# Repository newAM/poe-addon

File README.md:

# PoE Addon

Simple board to add power over Ethernet to a project.

This uses the [Wiznet W5500] for TCP/IP offload, and a [Microchip 25AA02E48] for
a valid EUI-48 MAC address.

## Bill of Materials

A bill of materials generated by [InteractiveHtmlBom] can be viewed at <https://newam.github.io/poe-addon/>

## Media

## Software Used

- [KiCad](http://kicad.org/) 7.0.0 release

[InteractiveHtmlBom]: https://github.com/openscopeproject/InteractiveHtmlBom/issues
[Wiznet W5500]: https://www.wiznet.io/product-item/w5500/
[Microchip 25AA02E48]: http://ww1.microchip.com/downloads/en/devicedoc/22123a.pdf

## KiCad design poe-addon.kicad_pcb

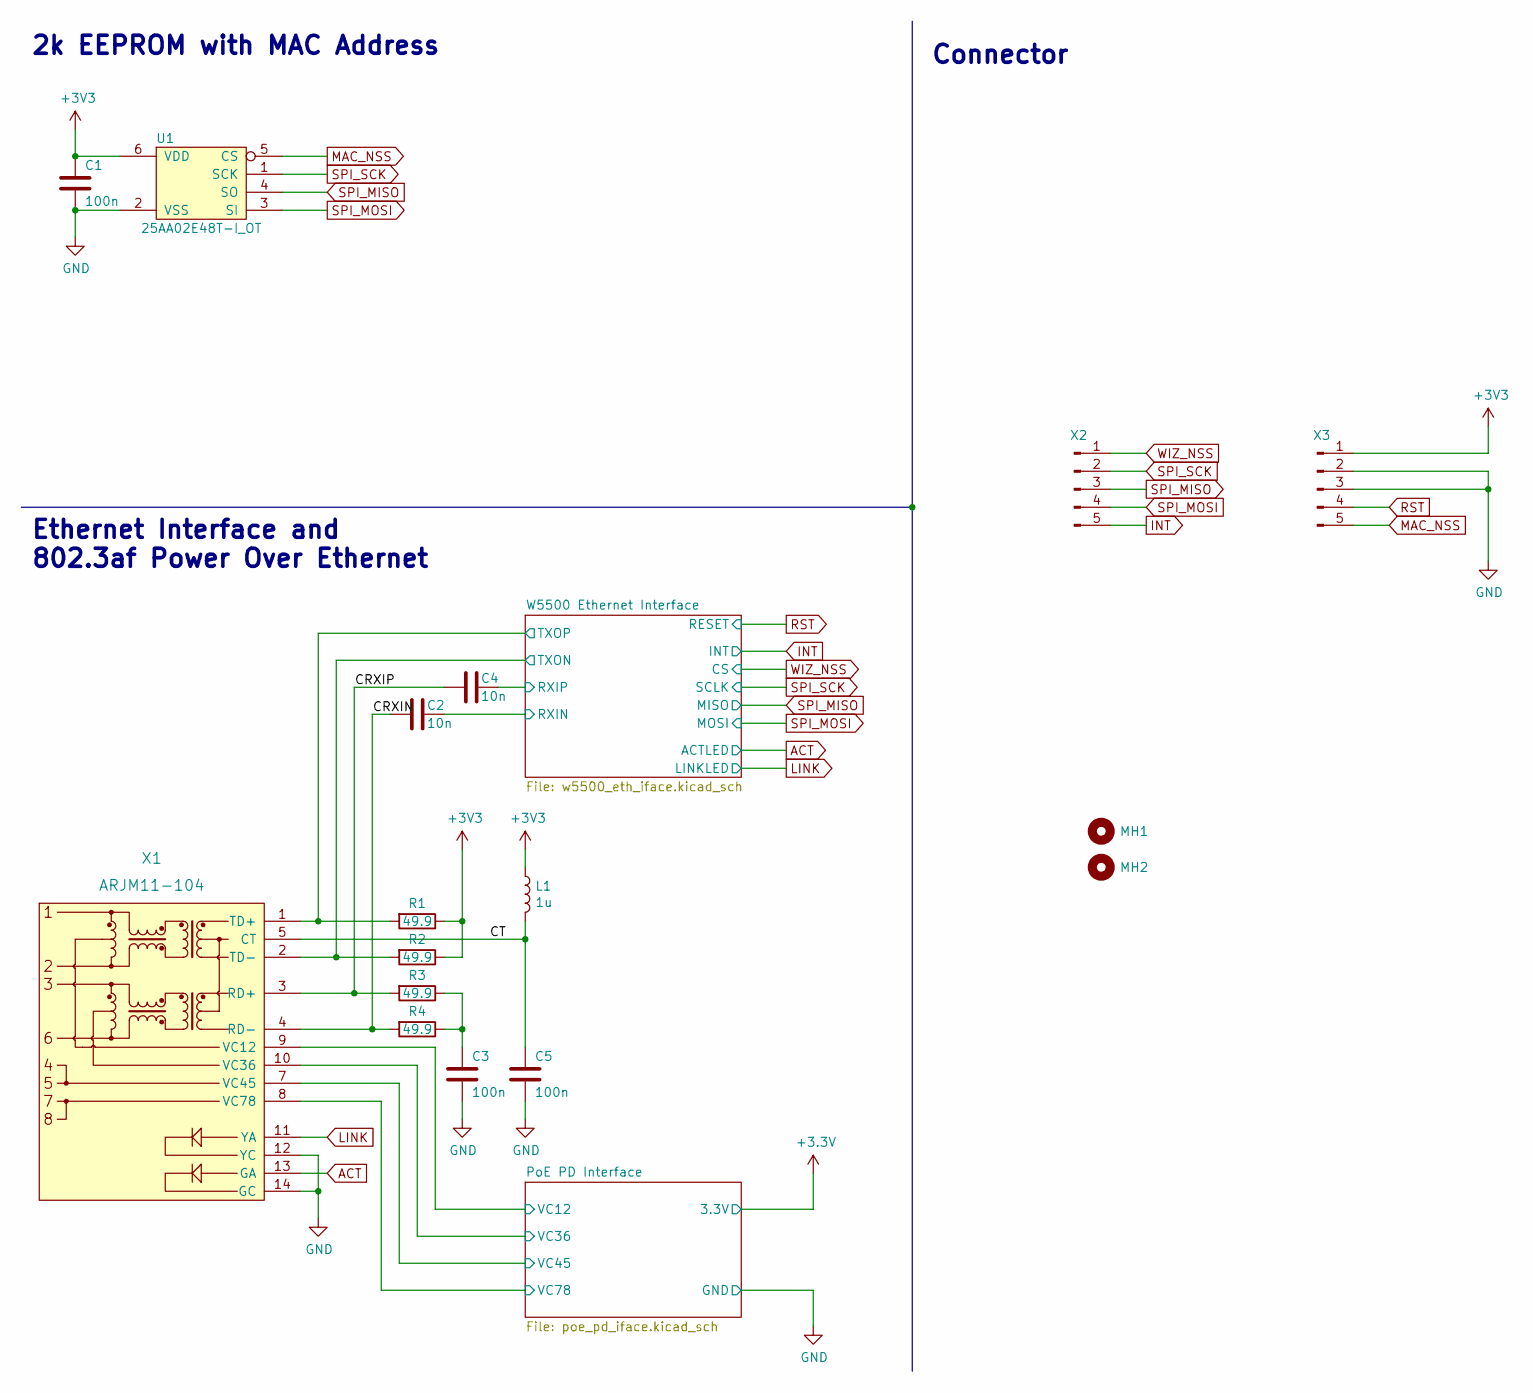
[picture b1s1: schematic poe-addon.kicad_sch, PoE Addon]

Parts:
C1, C3, C5: 100n; C_0603_1608Metric; Tolerance 10%; Voltage 16; DigiKey Part Number 1276-1005-1-ND
C2, C4: 10n; C_0603_1608Metric; Tolerance 10%; Voltage 50V; DigiKey Part Number 1276-1009-1-ND
L1: 1u; L_0603_1608Metric; Tolerance 20%; DigiKey Part Number 445-3163-1-ND
MH1, MH2: MountingHole; MountingHole_3.2mm_M3
R1, R2, R3, R4: 49.9; R_0805_2012Metric; Tolerance 1%; DigiKey Part Number RNCP0805FTD49R9CT-ND
U1: 25AA02E48T-I_OT; SOT-23-6; DigiKey Part Number 25AA02E48T-I/OT
X1: ARJM11-104; ARJM11D7-104-AB-EW2; DigiKey Part Number 535-14150-ND
X2, X3: Conn_01x05_Male; PinHeader_1x05_P2.54mm_Vertical

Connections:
/CRXIN: C2.2, R4.2, X1.4 (RD-)
/CRXIP: C4.2, R3.2, X1.3 (RD+)
/CT: C5.1, L1.2, X1.5 (CT)
/PoE PD Interface/VC12: X1.9 (VC12); also elsewhere on the board
/PoE PD Interface/VC36: X1.10 (VC36); also elsewhere on the board
/PoE PD Interface/VC45: X1.7 (VC45); also elsewhere on the board
/PoE PD Interface/VC78: X1.8 (VC78); also elsewhere on the board
/W5500 Ethernet Interface/RXIN: C2.1; also elsewhere on the board
/W5500 Ethernet Interface/RXIP: C4.1; also elsewhere on the board
/W5500 Ethernet Interface/TXON: R2.2, X1.2 (TD-); also elsewhere on the board
/W5500 Ethernet Interface/TXOP: R1.2, X1.1 (TD+); also elsewhere on the board
ACT: X1.13 (GA); also elsewhere on the board
GND: C1.2, C3.2, C5.2, U1.2 (VSS), X1.12 (YC), X1.14 (GC), X3.2, X3.3; also elsewhere on the board
INT: X2.5; also elsewhere on the board
LINK: X1.11 (YA); also elsewhere on the board
MAC_NSS: U1.5 (CS), X3.5
unnamed: C3.1, R3.1, R4.1
RST: X3.4; also elsewhere on the board
SPI_MISO: U1.4 (SO), X2.3; also elsewhere on the board
SPI_MOSI: U1.3 (SI), X2.4; also elsewhere on the board
SPI_SCK: U1.1 (SCK), X2.2; also elsewhere on the board
WIZ_NSS: X2.1; also elsewhere on the board

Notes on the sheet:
2k EEPROM with MAC Address
Connector
Ethernet Interface and 802.3af Power Over Ethernet

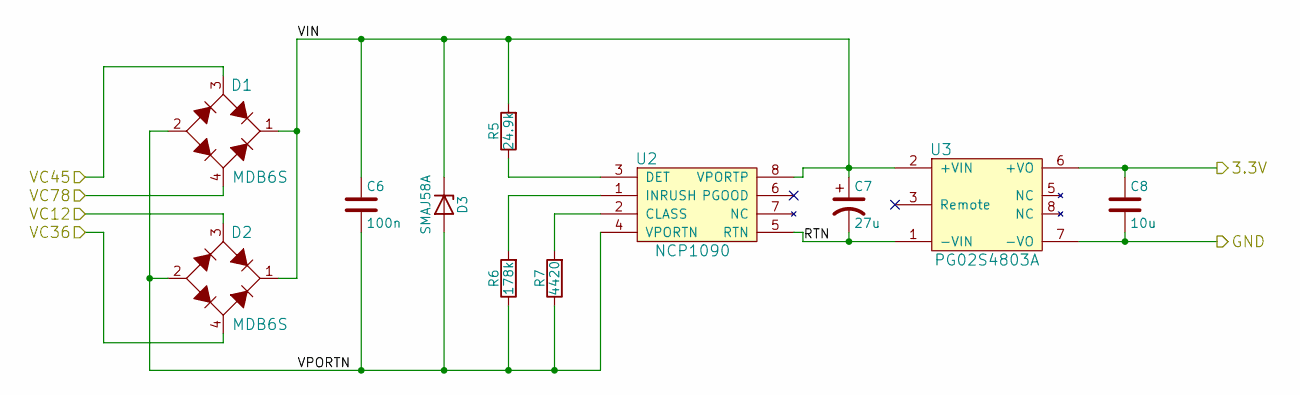
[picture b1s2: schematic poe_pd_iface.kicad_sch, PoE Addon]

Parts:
C6: 100n; C_0805_2012Metric; DigiKey Part Number 1276-6840-1-ND
C7: 27u; CP_Elec_8x10.5; DigiKey Part Number 399-A768KE276M1JLAE054CT-ND
C8: 10u; C_0805_2012Metric; DigiKey Part Number 1276-6456-1-ND
D1, D2: MDB6S; Micro-DIP-4; DigiKey Part Number MDB6SFSCT-ND
D3: SMAJ58A; D_SMA; DigiKey Part Number SMAJ58A-E3/61GICT-ND
R5: 24.9k; R_0603_1608Metric; DigiKey Part Number 311-24.9KHRCT-ND
R6: 178k; R_0603_1608Metric; DigiKey Part Number 311-178KHRCT-ND
R7: 4420; R_0603_1608Metric; DigiKey Part Number 311-4.42KHRCT-ND
U2: NCP1090; SOIC-8_3.9x4.9mm_P1.27mm; DigiKey Part Number NCP1090DRGOSCT-ND
U3: PG02S4803A; PG02S; DigiKey Part Number 941-1185-ND

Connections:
/PoE PD Interface/RTN: C7.2, U2.5 (RTN), U3.1 (-VIN)
/PoE PD Interface/VC12: D2.3 (AC1); also elsewhere on the board
/PoE PD Interface/VC36: D2.4 (AC2); also elsewhere on the board
/PoE PD Interface/VC45: D1.3 (AC1); also elsewhere on the board
/PoE PD Interface/VC78: D1.4 (AC2); also elsewhere on the board
/PoE PD Interface/VIN: C6.1, C7.1, D1.1 (+), D2.1 (+), D3.1 (K), R5.2, U2.8 (VPORTP), U3.2 (+VIN)
/PoE PD Interface/VPORTN: C6.2, D1.2 (-), D2.2 (-), D3.2 (A), R6.1, R7.1, U2.4 (VPORTN)
GND: C8.2, U3.7 (-VO); also elsewhere on the board
unnamed: R5.1, U2.3 (DET)
unnamed: R6.2, U2.1 (INRUSH)
unnamed: R7.2, U2.2 (CLASS)

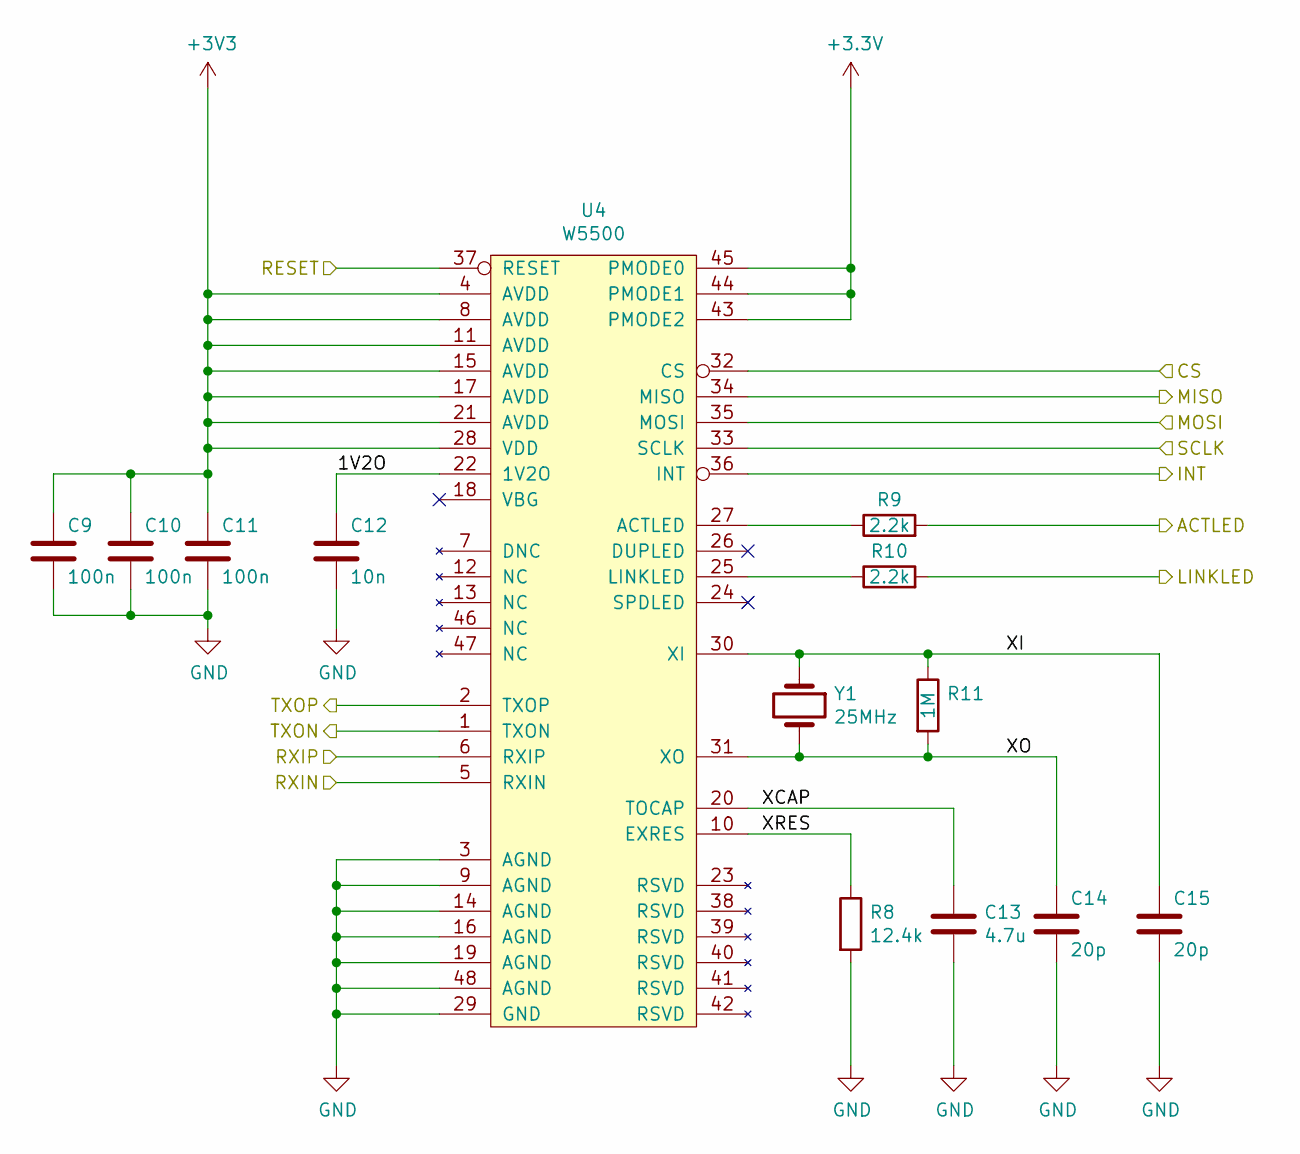
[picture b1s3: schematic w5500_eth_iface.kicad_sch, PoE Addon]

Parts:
C9, C10, C11: 100n; C_0603_1608Metric; DigiKey Part Number 1276-1012-1-ND
C12: 10n; C_0603_1608Metric; DigiKey Part Number 1276-1009-1-ND
C13: 4.7u; C_0603_1608Metric; DigiKey Part Number 1276-1907-1-ND
C14, C15: 20p; C_0603_1608Metric; DigiKey Part Number 1276-1187-1-ND
R8: 12.4k; R_0603_1608Metric; Tolerance ±1%; DigiKey Part Number 311-12.4KHRCT-ND
R9, R10: 2.2k; R_0603_1608Metric; DigiKey Part Number 311-2.20KHRCT-ND
R11: 1M; R_0603_1608Metric; DigiKey Part Number 311-1.0MGRCT-ND
U4: W5500; LQFP-48_7x7mm_P0.5mm; DigiKey Part Number 1278-1021-ND
Y1: 25MHz; Crystal_SMD_5032-2Pin_5.0x3.2mm; DigiKey Part Number CTX1175CT-ND

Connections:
/W5500 Ethernet Interface/1V2O: C12.1, U4.22 (1V2O)
/W5500 Ethernet Interface/RXIN: U4.5 (RXIN); also elsewhere on the board
/W5500 Ethernet Interface/RXIP: U4.6 (RXIP); also elsewhere on the board
/W5500 Ethernet Interface/TXON: U4.1 (TXON); also elsewhere on the board
/W5500 Ethernet Interface/TXOP: U4.2 (TXOP); also elsewhere on the board
/W5500 Ethernet Interface/XCAP: C13.1, U4.20 (TOCAP)
/W5500 Ethernet Interface/XI: C15.1, R11.1, U4.30 (XI), Y1.1
/W5500 Ethernet Interface/XO: C14.1, R11.2, U4.31 (XO), Y1.2
/W5500 Ethernet Interface/XRES: R8.1, U4.10 (EXRES)
ACT: R9.2; also elsewhere on the board
GND: C9.2, C10.2, C11.2, C12.2, C13.2, C14.2, C15.2, R8.2, U4.3 (AGND), U4.9 (AGND), U4.14 (AGND), U4.16 (AGND), U4.19 (AGND), U4.29 (GND), U4.48 (AGND); also elsewhere on the board
INT: U4.36 (INT); also elsewhere on the board
LINK: R10.2; also elsewhere on the board
unnamed: R9.1, U4.27 (ACTLED)
unnamed: R10.1, U4.25 (LINKLED)
RST: U4.37 (RESET); also elsewhere on the board
SPI_MISO: U4.34 (MISO); also elsewhere on the board
SPI_MOSI: U4.35 (MOSI); also elsewhere on the board
SPI_SCK: U4.33 (SCLK); also elsewhere on the board
WIZ_NSS: U4.32 (CS); also elsewhere on the board

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
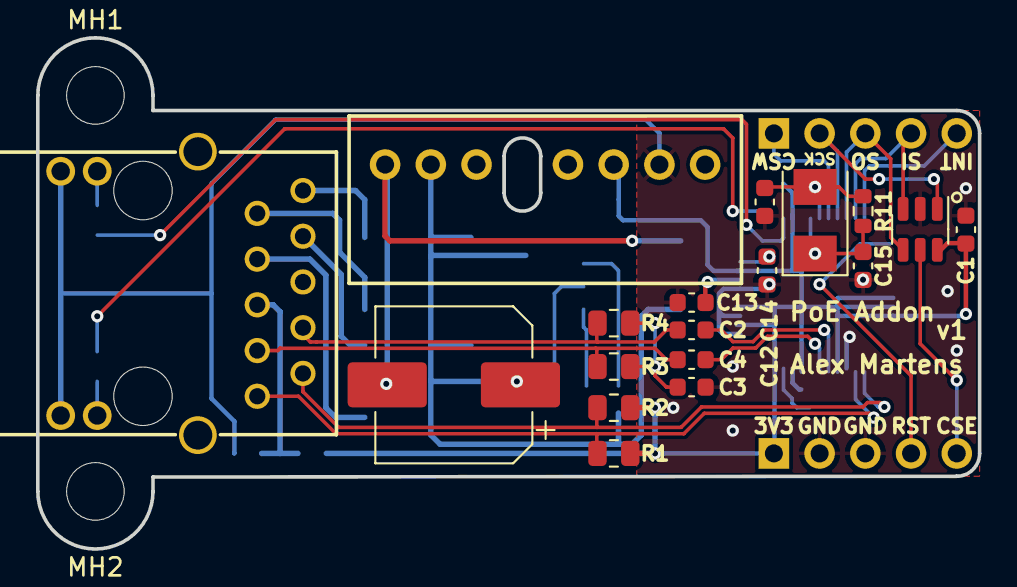
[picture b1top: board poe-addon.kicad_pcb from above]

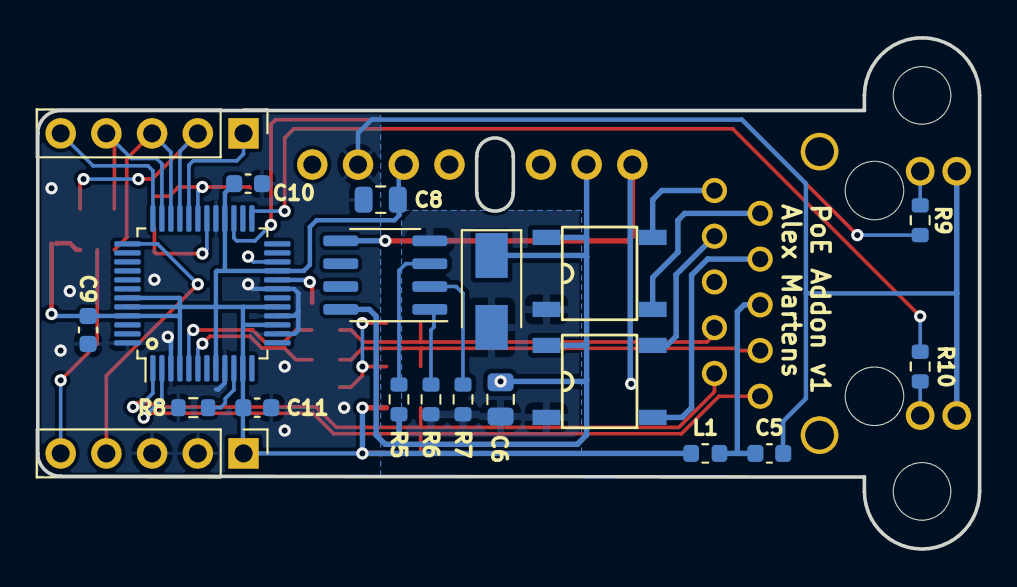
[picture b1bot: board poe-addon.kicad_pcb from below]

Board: 2 copper layers, 52.3 x 28.4 mm, 40 parts (20 on the bottom side), 36 nets.

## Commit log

2022-04-15 fix typo
2022-06-26 add pg02s 3D model
2022-06-26 Add interactive bill of materials
2022-06-26 README: add link to BOM
2022-06-26 bom: add digikey part numbers
2022-06-26 10nF 0603: 1276-1921-1-ND -> 1276-1009-1-ND
2022-06-26 NCP1090: NCP1090DGOS-ND -> NCP1090DRGOSCT-ND
2022-06-26 22uF electrolytic: replace with 27uF for stock reasons
    399-A768KE226M1JLAE054TR-ND -> 399-A768KE276M1JLAE054CT-ND
2022-06-26 w5500 crystal: CTX1437CT-ND -> CTX1175CT-ND
2022-06-27 add mounting holes, replace magjack with in-stock part
2022-06-27 flake.nix: remove patch from InteractiveHtmlBom
2022-06-27 update date
2022-06-27 deploy: e2dd724646c237e0e1d556927b6f1ff099d4cfc5
2022-10-13 CI: bump cachix actions
2022-10-28 Bump cachix/cachix-action from 11 to 12
    Bumps [cachix/cachix-action](https://github.com/cachix/cachix-action) from 11 to 12.
    - [Release notes](https://github.com/cachix/cachix-action/releases)
    - [Commits](https://github.com/cachix/cachix-action/compare/v11...v12)
    ---
    updated-dependencies:
    - dependency-name: cachix/cachix-action
2023-02-07 Bump cachix/install-nix-action from 18 to 19
    Bumps [cachix/install-nix-action](https://github.com/cachix/install-nix-action) from 18 to 19.
    - [Release notes](https://github.com/cachix/install-nix-action/releases)
    - [Commits](https://github.com/cachix/install-nix-action/compare/v18...v19)
    ---
    updated-dependencies:
    - dependency-name: cachix/install-nix-action
2023-03-02 Bump cachix/install-nix-action from 19 to 20
    Bumps [cachix/install-nix-action](https://github.com/cachix/install-nix-action) from 19 to 20.
    - [Release notes](https://github.com/cachix/install-nix-action/releases)
    - [Commits](https://github.com/cachix/install-nix-action/compare/v19...v20)
    ---
    updated-dependencies:
    - dependency-name: cachix/install-nix-action
2023-05-25 Bump cachix/install-nix-action from 20 to 21
    Bumps [cachix/install-nix-action](https://github.com/cachix/install-nix-action) from 20 to 21.
    - [Release notes](https://github.com/cachix/install-nix-action/releases)
    - [Commits](https://github.com/cachix/install-nix-action/compare/v20...v21)
    ---
    updated-dependencies:
    - dependency-name: cachix/install-nix-action
2023-06-19 Bump cachix/install-nix-action from 21 to 22
    Bumps [cachix/install-nix-action](https://github.com/cachix/install-nix-action) from 21 to 22.
    - [Release notes](https://github.com/cachix/install-nix-action/releases)
    - [Commits](https://github.com/cachix/install-nix-action/compare/v21...v22)
    ---
    updated-dependencies:
    - dependency-name: cachix/install-nix-action
2023-07-15 flake.lock: update
    • Updated input 'nixpkgs':
    'github:nixos/nixpkgs/f2537a505d45c31fe5d9c27ea9829b6f4c4e6ac5' (2022-06-26)
    → 'github:nixos/nixpkgs/e74e68449c385db82de3170288a28cd0f608544f' (2023-07-13)
2023-07-18 Add LCSC part numbers
2023-09-05 Bump actions/checkout from 3 to 4
    Bumps [actions/checkout](https://github.com/actions/checkout) from 3 to 4.
    - [Release notes](https://github.com/actions/checkout/releases)
    - [Changelog](https://github.com/actions/checkout/blob/main/CHANGELOG.md)
    - [Commits](https://github.com/actions/checkout/compare/v3...v4)
    ---
    updated-dependencies:
2023-09-05 Bump cachix/install-nix-action from 22 to 23
    Bumps [cachix/install-nix-action](https://github.com/cachix/install-nix-action) from 22 to 23.
    - [Release notes](https://github.com/cachix/install-nix-action/releases)
    - [Commits](https://github.com/cachix/install-nix-action/compare/v22...v23)
    ---
    updated-dependencies:
    - dependency-name: cachix/install-nix-action
2023-11-29 Bump cachix/cachix-action from 12 to 13
    Bumps [cachix/cachix-action](https://github.com/cachix/cachix-action) from 12 to 13.
    - [Release notes](https://github.com/cachix/cachix-action/releases)
    - [Commits](https://github.com/cachix/cachix-action/compare/v12...v13)
    ---
    updated-dependencies:
    - dependency-name: cachix/cachix-action
2023-11-29 Bump cachix/install-nix-action from 23 to 24
    Bumps [cachix/install-nix-action](https://github.com/cachix/install-nix-action) from 23 to 24.
    - [Release notes](https://github.com/cachix/install-nix-action/releases)
    - [Commits](https://github.com/cachix/install-nix-action/compare/v23...v24)
    ---
    updated-dependencies:
    - dependency-name: cachix/install-nix-action
2024-01-15 Bump cachix/cachix-action from 13 to 14
    Bumps [cachix/cachix-action](https://github.com/cachix/cachix-action) from 13 to 14.
    - [Release notes](https://github.com/cachix/cachix-action/releases)
    - [Commits](https://github.com/cachix/cachix-action/compare/v13...v14)
    ---
    updated-dependencies:
    - dependency-name: cachix/cachix-action
2024-01-15 Bump cachix/install-nix-action from 24 to 25
    Bumps [cachix/install-nix-action](https://github.com/cachix/install-nix-action) from 24 to 25.
    - [Release notes](https://github.com/cachix/install-nix-action/releases)
    - [Commits](https://github.com/cachix/install-nix-action/compare/v24...v25)
    ---
    updated-dependencies:
    - dependency-name: cachix/install-nix-action
2024-03-11 Bump cachix/install-nix-action from 25 to 26
    Bumps [cachix/install-nix-action](https://github.com/cachix/install-nix-action) from 25 to 26.
    - [Release notes](https://github.com/cachix/install-nix-action/releases)
    - [Commits](https://github.com/cachix/install-nix-action/compare/v25...v26)
    ---
    updated-dependencies:
    - dependency-name: cachix/install-nix-action
2024-03-11 deploy: a0d292fb40ba356467e4ff22967a3d7208598238
2024-04-09 Bump peaceiris/actions-gh-pages from 3 to 4
    Bumps [peaceiris/actions-gh-pages](https://github.com/peaceiris/actions-gh-pages) from 3 to 4.
    - [Release notes](https://github.com/peaceiris/actions-gh-pages/releases)
    - [Changelog](https://github.com/peaceiris/actions-gh-pages/blob/main/CHANGELOG.md)
    - [Commits](https://github.com/peaceiris/actions-gh-pages/compare/v3...v4)
    ---
    updated-dependencies:
2024-05-07 github-actions: update
2024-05-16 Bump cachix/install-nix-action from 26 to 27
    Bumps [cachix/install-nix-action](https://github.com/cachix/install-nix-action) from 26 to 27.
    - [Release notes](https://github.com/cachix/install-nix-action/releases)
    - [Commits](https://github.com/cachix/install-nix-action/compare/v26...V27)
    ---
    updated-dependencies:
    - dependency-name: cachix/install-nix-action
2024-05-21 --- updated-dependencies: - dependency-name: cachix/cachix-action dependency-type: direct:production update-type: version-update:semver-major ...
2024-09-01 README: add media of real device
2024-09-01 flake: add checks
2024-09-01 flake.lock: update
    • Updated input 'interactive-html-bom':
    'github:newam/interactive-html-bom-nix/456e86bd2550811073850cde7699b7779c54eb7f' (2022-06-26)
    → 'github:newam/interactive-html-bom-nix/d7c659eca0a94c0a75543d699e1024d84583afdf' (2024-09-01)
    • Updated input 'nixpkgs':
    'github:nixos/nixpkgs/e74e68449c385db82de3170288a28cd0f608544f' (2023-07-13)
    → 'github:nixos/nixpkgs/12228ff1752d7b7624a54e9c1af4b222b3c1073b' (2024-08-31)
2024-09-13 Bump cachix/install-nix-action from V27 to 28
    Bumps [cachix/install-nix-action](https://github.com/cachix/install-nix-action) from V27 to 28. This release includes the previously tagged commit.
    - [Release notes](https://github.com/cachix/install-nix-action/releases)
    - [Commits](https://github.com/cachix/install-nix-action/compare/V27...V28)
    ---
    updated-dependencies:
    - dependency-name: cachix/install-nix-action
2024-09-27 Bump cachix/install-nix-action from V28 to 29
    Bumps [cachix/install-nix-action](https://github.com/cachix/install-nix-action) from V28 to 29. This release includes the previously tagged commit.
    - [Release notes](https://github.com/cachix/install-nix-action/releases)
    - [Commits](https://github.com/cachix/install-nix-action/compare/V28...v29)
    ---
    updated-dependencies:
    - dependency-name: cachix/install-nix-action
2024-10-04 Bump cachix/install-nix-action from 29 to 30
    Bumps [cachix/install-nix-action](https://github.com/cachix/install-nix-action) from 29 to 30.
    - [Release notes](https://github.com/cachix/install-nix-action/releases)
    - [Commits](https://github.com/cachix/install-nix-action/compare/v29...v30)
    ---
    updated-dependencies:
    - dependency-name: cachix/install-nix-action
2025-03-11 Bump cachix/install-nix-action from 30 to 31
    Bumps [cachix/install-nix-action](https://github.com/cachix/install-nix-action) from 30 to 31.
    - [Release notes](https://github.com/cachix/install-nix-action/releases)
    - [Commits](https://github.com/cachix/install-nix-action/compare/v30...v31)
    ---
    updated-dependencies:
    - dependency-name: cachix/install-nix-action
2025-03-11 Bump cachix/cachix-action from 15 to 16
    Bumps [cachix/cachix-action](https://github.com/cachix/cachix-action) from 15 to 16.
    - [Release notes](https://github.com/cachix/cachix-action/releases)
    - [Commits](https://github.com/cachix/cachix-action/compare/v15...v16)
    ---
    updated-dependencies:
    - dependency-name: cachix/cachix-action
2025-08-12 Bump actions/checkout from 4 to 5
    Bumps [actions/checkout](https://github.com/actions/checkout) from 4 to 5.
    - [Release notes](https://github.com/actions/checkout/releases)
    - [Changelog](https://github.com/actions/checkout/blob/main/CHANGELOG.md)
    - [Commits](https://github.com/actions/checkout/compare/v4...v5)
    ---
    updated-dependencies:
2025-08-25 Bump actions/upload-pages-artifact from 3 to 4
    Bumps [actions/upload-pages-artifact](https://github.com/actions/upload-pages-artifact) from 3 to 4.
    - [Release notes](https://github.com/actions/upload-pages-artifact/releases)
    - [Commits](https://github.com/actions/upload-pages-artifact/compare/v3...v4)
    ---
    updated-dependencies:
    - dependency-name: actions/upload-pages-artifact
2025-11-21 Bump actions/checkout from 5 to 6
    Bumps [actions/checkout](https://github.com/actions/checkout) from 5 to 6.
    - [Release notes](https://github.com/actions/checkout/releases)
    - [Changelog](https://github.com/actions/checkout/blob/main/CHANGELOG.md)
    - [Commits](https://github.com/actions/checkout/compare/v5...v6)
    ---
    updated-dependencies:
2026-03-19 Bump cachix/cachix-action from 16 to 17
    Bumps [cachix/cachix-action](https://github.com/cachix/cachix-action) from 16 to 17.
    - [Release notes](https://github.com/cachix/cachix-action/releases)
    - [Commits](https://github.com/cachix/cachix-action/compare/v16...v17)
    ---
    updated-dependencies:
    - dependency-name: cachix/cachix-action
2026-03-26 Bump actions/deploy-pages from 4 to 5
    Bumps [actions/deploy-pages](https://github.com/actions/deploy-pages) from 4 to 5.
    - [Release notes](https://github.com/actions/deploy-pages/releases)
    - [Commits](https://github.com/actions/deploy-pages/compare/v4...v5)
    ---
    updated-dependencies:
    - dependency-name: actions/deploy-pages
2026-04-14 Bump actions/upload-pages-artifact from 4 to 5
    Bumps [actions/upload-pages-artifact](https://github.com/actions/upload-pages-artifact) from 4 to 5.
    - [Release notes](https://github.com/actions/upload-pages-artifact/releases)
    - [Commits](https://github.com/actions/upload-pages-artifact/compare/v4...v5)
    ---
    updated-dependencies:
    - dependency-name: actions/upload-pages-artifact
2026-06-19 Bump actions/checkout from 6 to 7
    Bumps [actions/checkout](https://github.com/actions/checkout) from 6 to 7.
    - [Release notes](https://github.com/actions/checkout/releases)
    - [Changelog](https://github.com/actions/checkout/blob/main/CHANGELOG.md)
    - [Commits](https://github.com/actions/checkout/compare/v6...v7)
    ---
    updated-dependencies:
